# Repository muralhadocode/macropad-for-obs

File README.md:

# Macropad for obs :D
A custom hardware macropad that can change scenes, start and stop a stream and recording, and change the volume of the microphone and the volume of the desktop.
## Why did i build this?
Basically i joined hackclub because of the stickers and was too lazy to look into it -_-, but i thought for a moment, "hmmmm i know eletronics and i speak english, i should give it a try!", welp and so i did, i started with the idea of making the macropad in stardust but migrated to macondo because it was wayyyyyyyy better than stardust (i didnt do anything there tho just posted one devlog then left ;-;) and it took me a long time to do this thing, the idea came with a purpose too, a simple macropad that can help little youtubers and streamers (like me because my channel isnt that big -w-) basically it can change scenes, start and stop a stream and recording, and change the volume of the microphone and the volume of the desktop, wich is some of the key features that could be acessed easily trought the macropad :D 

## How it works
The project consists of a custom PCB designed in KiCad, featuring 5 buttons (1 for changing scene, 1 for starting a stream, 1 for stopping a stream, 1 for starting a recording and one for stopping a recording) and 2 rotary encoders (1 for changing the volume of the microphone and one for changing the volume of the desktop) and an microcontroller Seeed Studio XIAO SAMD21.
The Firmware consist in making key shortcuts for the start and stop stream and recording, and for the change scene, since obs has no shortcut for changing the volume you need to download the ([obs midi plugin](https://github.com/nhielost/obs-midi-mg/)) so the encoders work, then you need to set it up:D.

## Pictures

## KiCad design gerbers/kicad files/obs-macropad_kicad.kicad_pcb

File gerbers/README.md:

# Gerber files
This folder contains the gerber and drill files for the PCB fabrication.

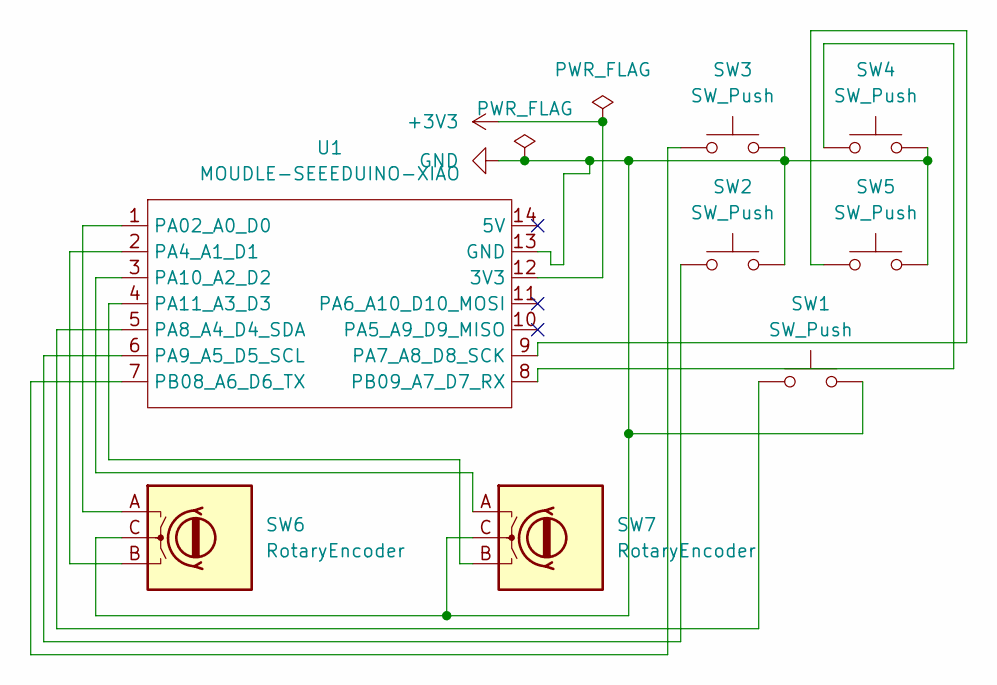
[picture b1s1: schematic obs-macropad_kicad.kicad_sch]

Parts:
SW1, SW2, SW3, SW4, SW5: SW_Push; SW_Cherry_MX_1.00u_PCB
SW6, SW7: RotaryEncoder; RotaryEncoder_Alps_EC11E-Switch_Vertical_H20mm
U1: MOUDLE-SEEEDUINO-XIAO; XIAO-Generic-Hybrid-14P-2.54-21X17.8MM

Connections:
+3V3: U1.12 (3V3)
/<NO NET>: SW7.B, U1.4 (PA11_A3_D3)
GND: SW1.2, SW2.2, SW3.2, SW4.2, SW5.2, SW6.C, SW7.C, U1.13 (GND)
unnamed: SW6.A, U1.1 (PA02_A0_D0)
unnamed: SW6.B, U1.2 (PA4_A1_D1)
unnamed: SW5.1, U1.9 (PA7_A8_D8_SCK)
unnamed: SW1.1, U1.5 (PA8_A4_D4_SDA)
unnamed: SW2.1, U1.6 (PA9_A5_D5_SCL)
unnamed: SW7.A, U1.3 (PA10_A2_D2)
unnamed: SW3.1, U1.7 (PB08_A6_D6_TX)
unnamed: SW4.1, U1.8 (PB09_A7_D7_RX)

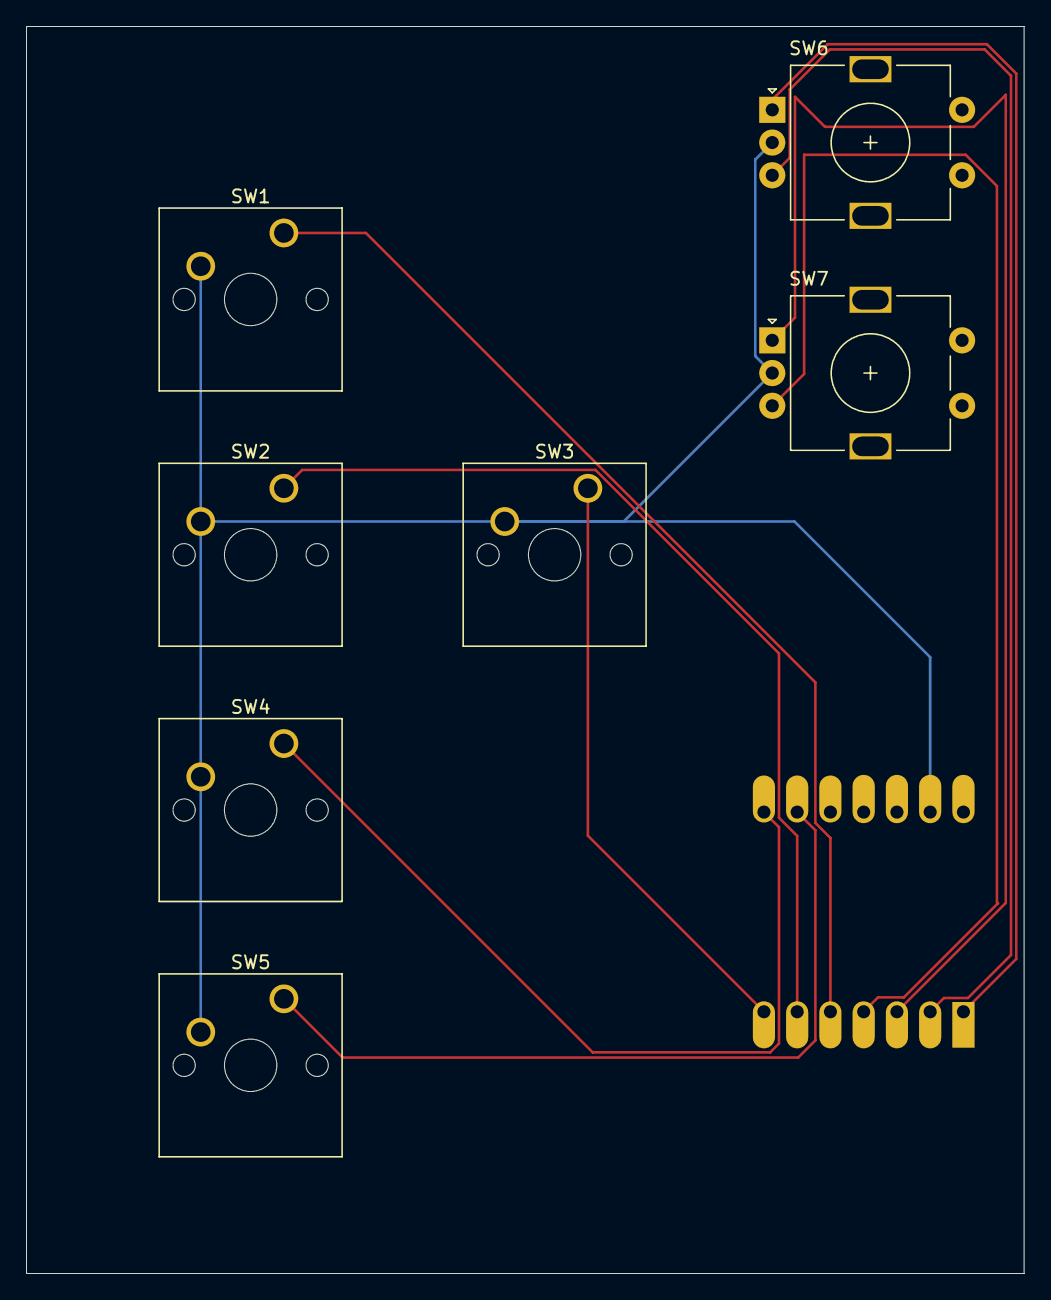
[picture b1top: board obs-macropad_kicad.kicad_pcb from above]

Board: 2 copper layers, 76.2 x 95.2 mm, 8 parts (1 on the bottom side), 10 nets.

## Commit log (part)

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2026-06-07 Just made the code, its a arduino file
2026-06-07 jsut added the encoder variables
2026-06-07 Finished the code
2026-06-07 Add MIT License to the project
2026-06-07 Update README.md with extra spacing
    Added additional spacing in the README file.
2026-06-07 Revise README with project details and features
    Updated project description and added sections on purpose and functionality.
2026-06-07 Almost finished the README.md just need to put the prints
2026-06-07 Rename section and add images to README
    Updated section title from 'Photos & Design' to 'Pictures' and added multiple images.
2026-06-07 Add Kicad and OS temp files to .gitignore
2026-06-07 Add README for Gerber files directory
2026-06-07 Create README.md for 3D case files
    Added README to explain the contents of the folder.
2026-06-07 Link for the OBS plugin added
2026-06-22 Revise images in README.md
    Updated images in the README to include new screenshots and remove outdated ones.
2026-06-23 Update README with project images
    Added images to the README to showcase the project.
2026-06-26 Create kicad
2026-06-26 Create idk
